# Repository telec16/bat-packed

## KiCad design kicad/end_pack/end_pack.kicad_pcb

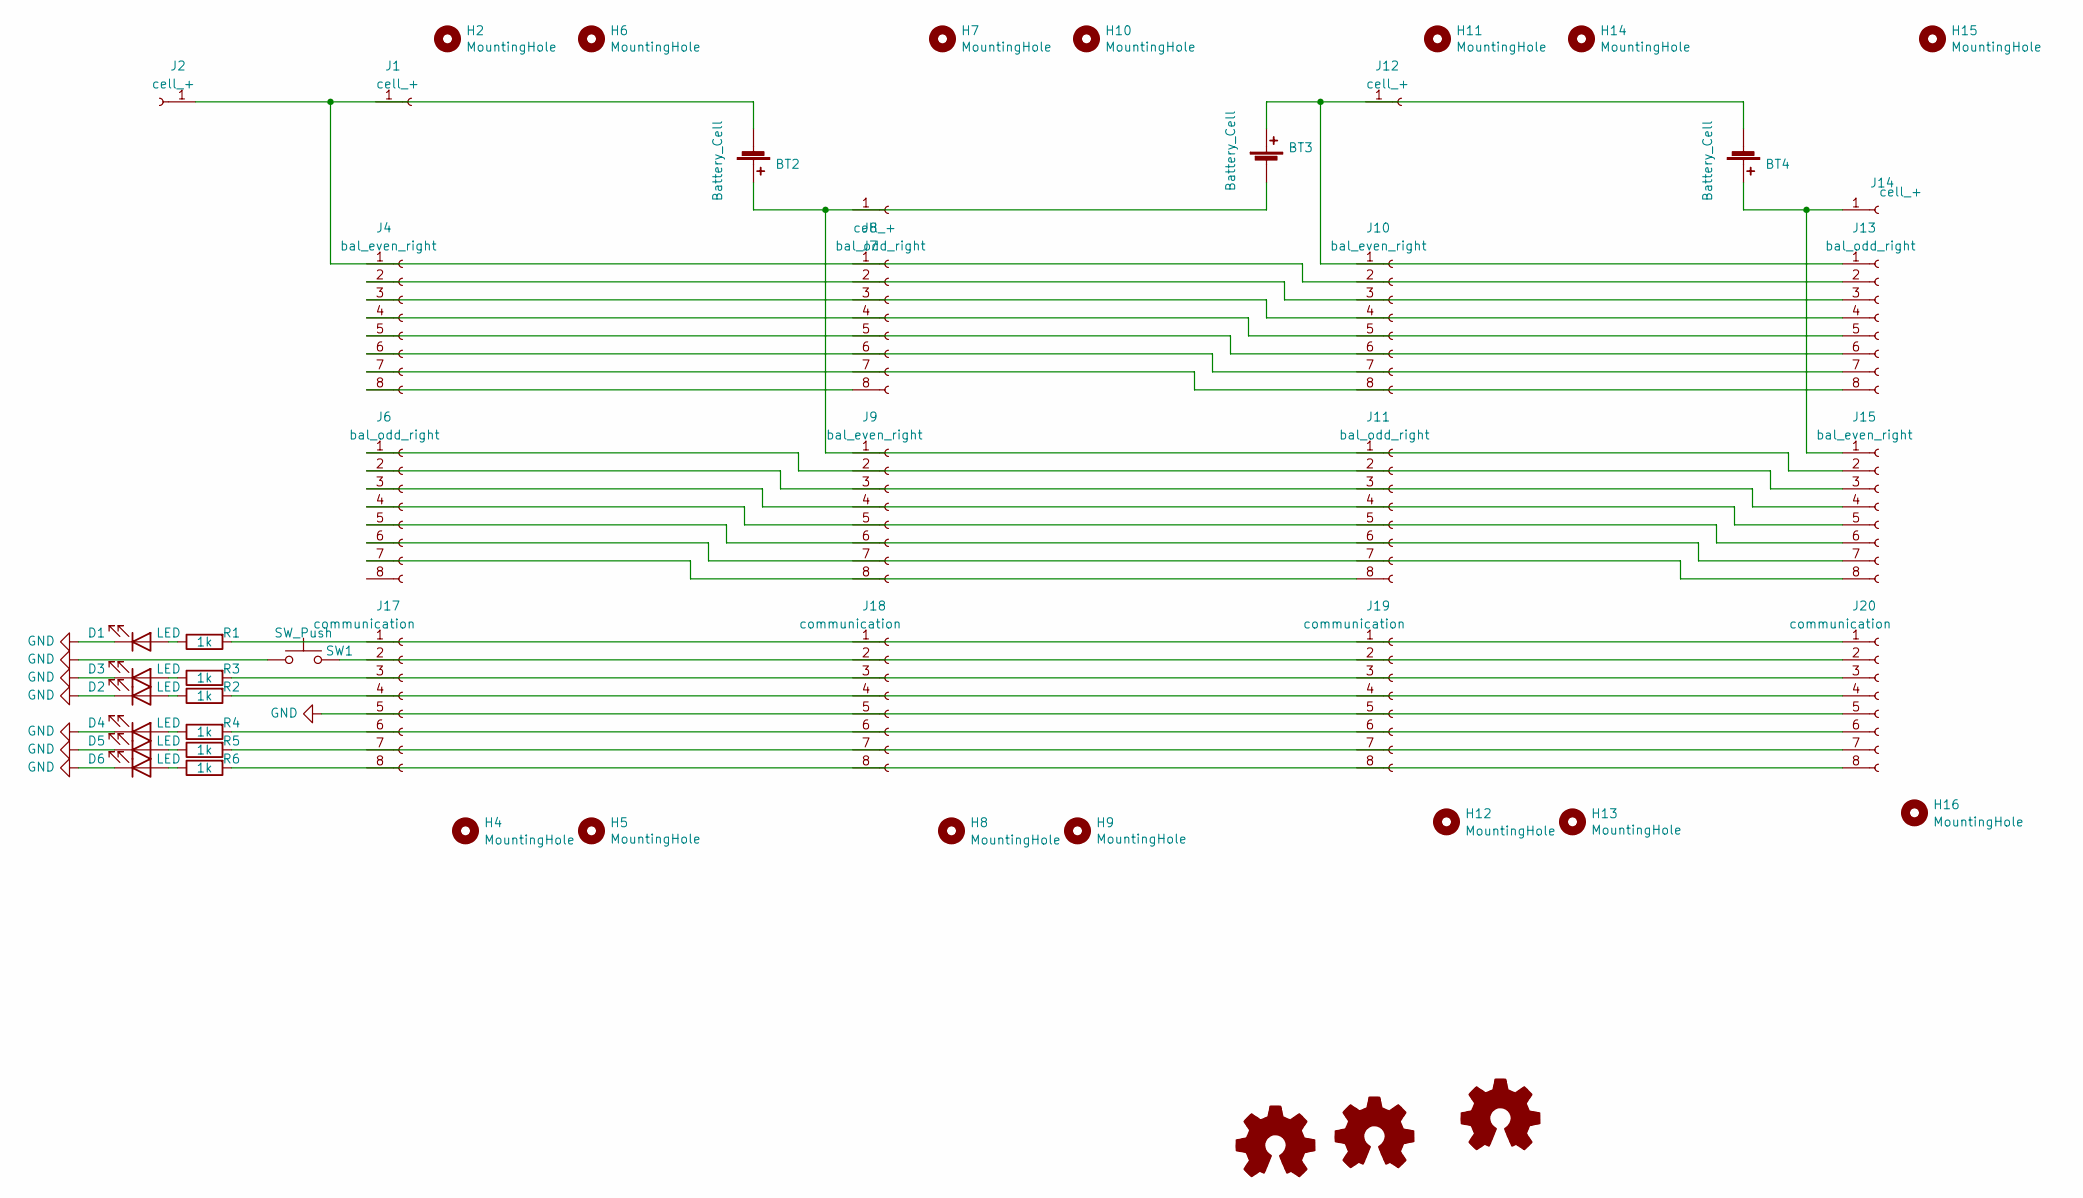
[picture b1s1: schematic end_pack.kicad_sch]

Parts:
BT2, BT3, BT4: Battery_Cell; Cell_18650
D1, D2, D3, D4, D5, D6: LED; LED_1206_3216Metric
H2, H4, H5, H6, H7, H8, H9, H10, H11, H12, H13, H14, H15, H16: MountingHole; MountingHole_2mm
J1, J7, J12: cell_+; Castellated_1x01_P5.08mm_Triple
J2: cell_+; Pin_D1.3mm_L11.0mm_LooseFit
J4, J9, J10, J15: bal_even_right; Castellated_1x08_P2.54mm
J6, J8, J11, J14: bal_odd_right; Castellated_1x08_P2.54mm
J13: cell_+; Castellated_1x01_P5.08mm_Double
J17, J18, J19, J20: communication; DualSide_2x05_P1.27mm_Vertical_SMD
LOGO1, LOGO2, LOGO3: Logo_Open_Hardware_Small; batpacked-24
R1, R2, R3, R4, R5, R6: 1k; R_0805_2012Metric
SW1: SW_Push; SW_Push_SPST_NO_Alps_SKRK

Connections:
GND: D1.1 (K), D2.1 (K), D3.1 (K), D4.1 (K), D5.1 (K), D6.1 (K), J20.5, SW1.2
unnamed: BT2.1 (+), BT3.2 (-), J15.2
unnamed: BT2.2 (-), J2.1, J14.2
unnamed: BT3.1 (+), BT4.2 (-), J14.1
unnamed: BT4.1 (+), J13.1, J15.1
unnamed: D1.2 (A), R1.1
unnamed: D2.2 (A), R2.1
unnamed: D3.2 (A), R3.1
unnamed: D4.2 (A), R4.1
unnamed: D5.2 (A), R5.1
unnamed: D6.2 (A), R6.1
unnamed: J4.8, J8.8
unnamed: J6.7, J11.8
unnamed: J4.2, J14.3
unnamed: J4.3, J14.4
unnamed: J4.4, J14.5
unnamed: J4.5, J14.6
unnamed: J4.6, J14.7
unnamed: J4.7, J14.8
unnamed: J6.1, J15.3
unnamed: J6.2, J15.4
unnamed: J6.3, J15.5
unnamed: J6.4, J15.6
unnamed: J6.5, J15.7
unnamed: J6.6, J15.8
unnamed: J20.1, R1.2
unnamed: J20.2, SW1.1
unnamed: J20.3, R3.2
unnamed: J20.4, R2.2
unnamed: J20.6, R4.2
unnamed: J20.7, R5.2
unnamed: J20.8, R6.2

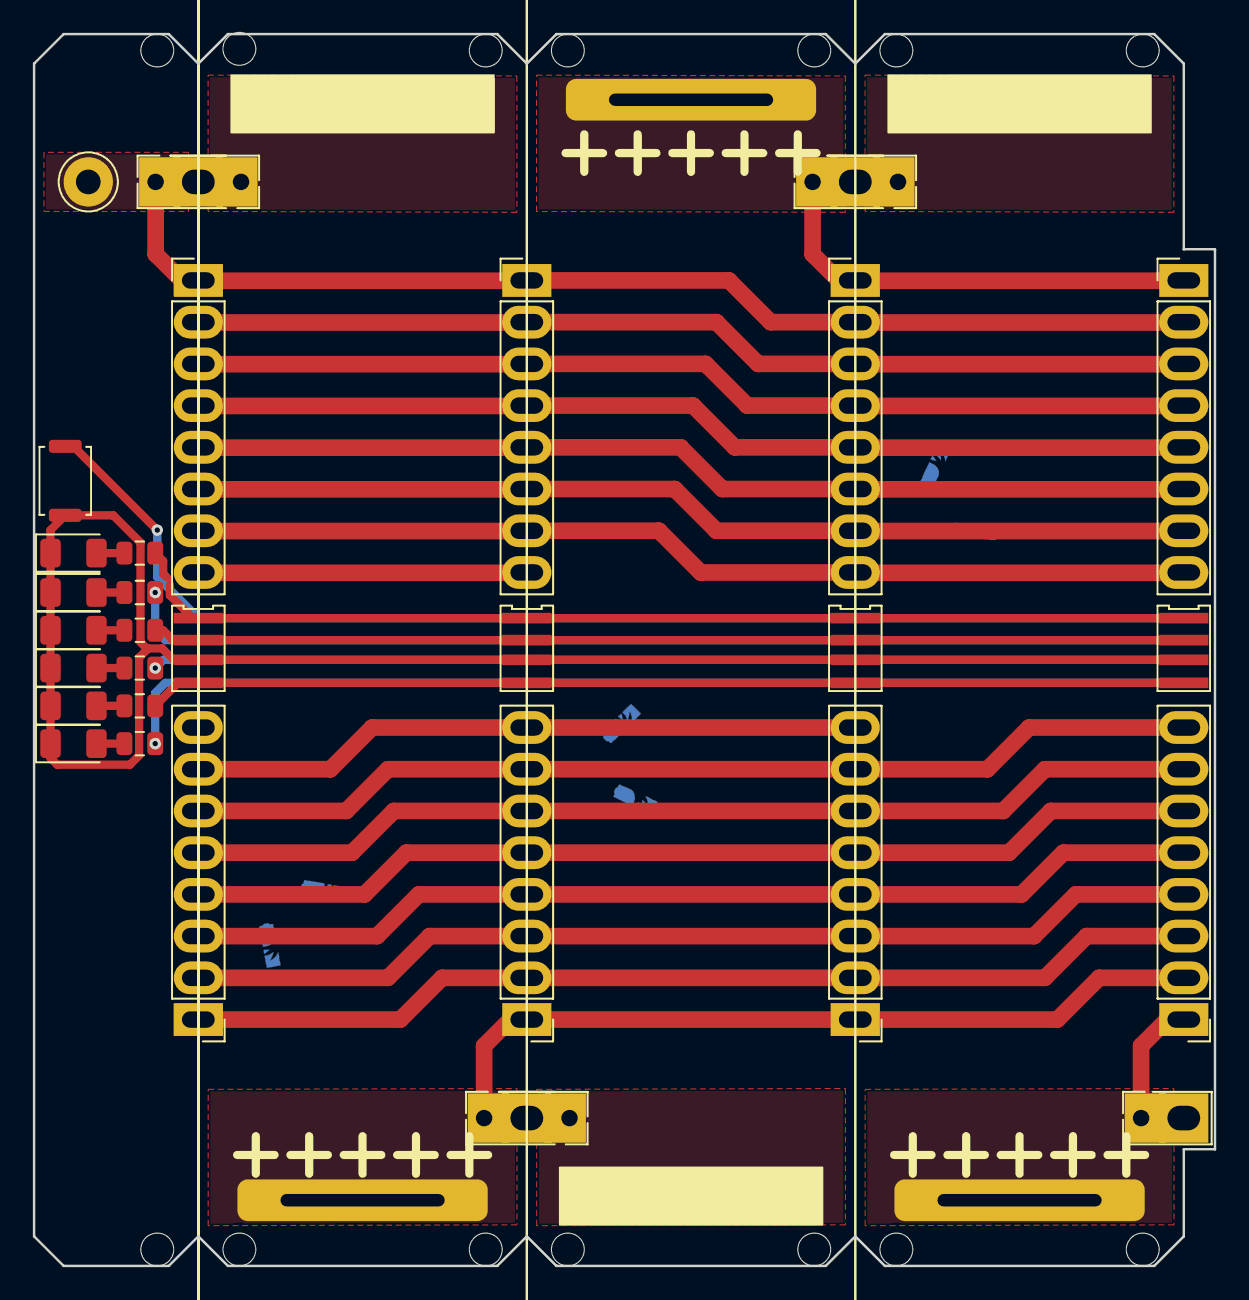
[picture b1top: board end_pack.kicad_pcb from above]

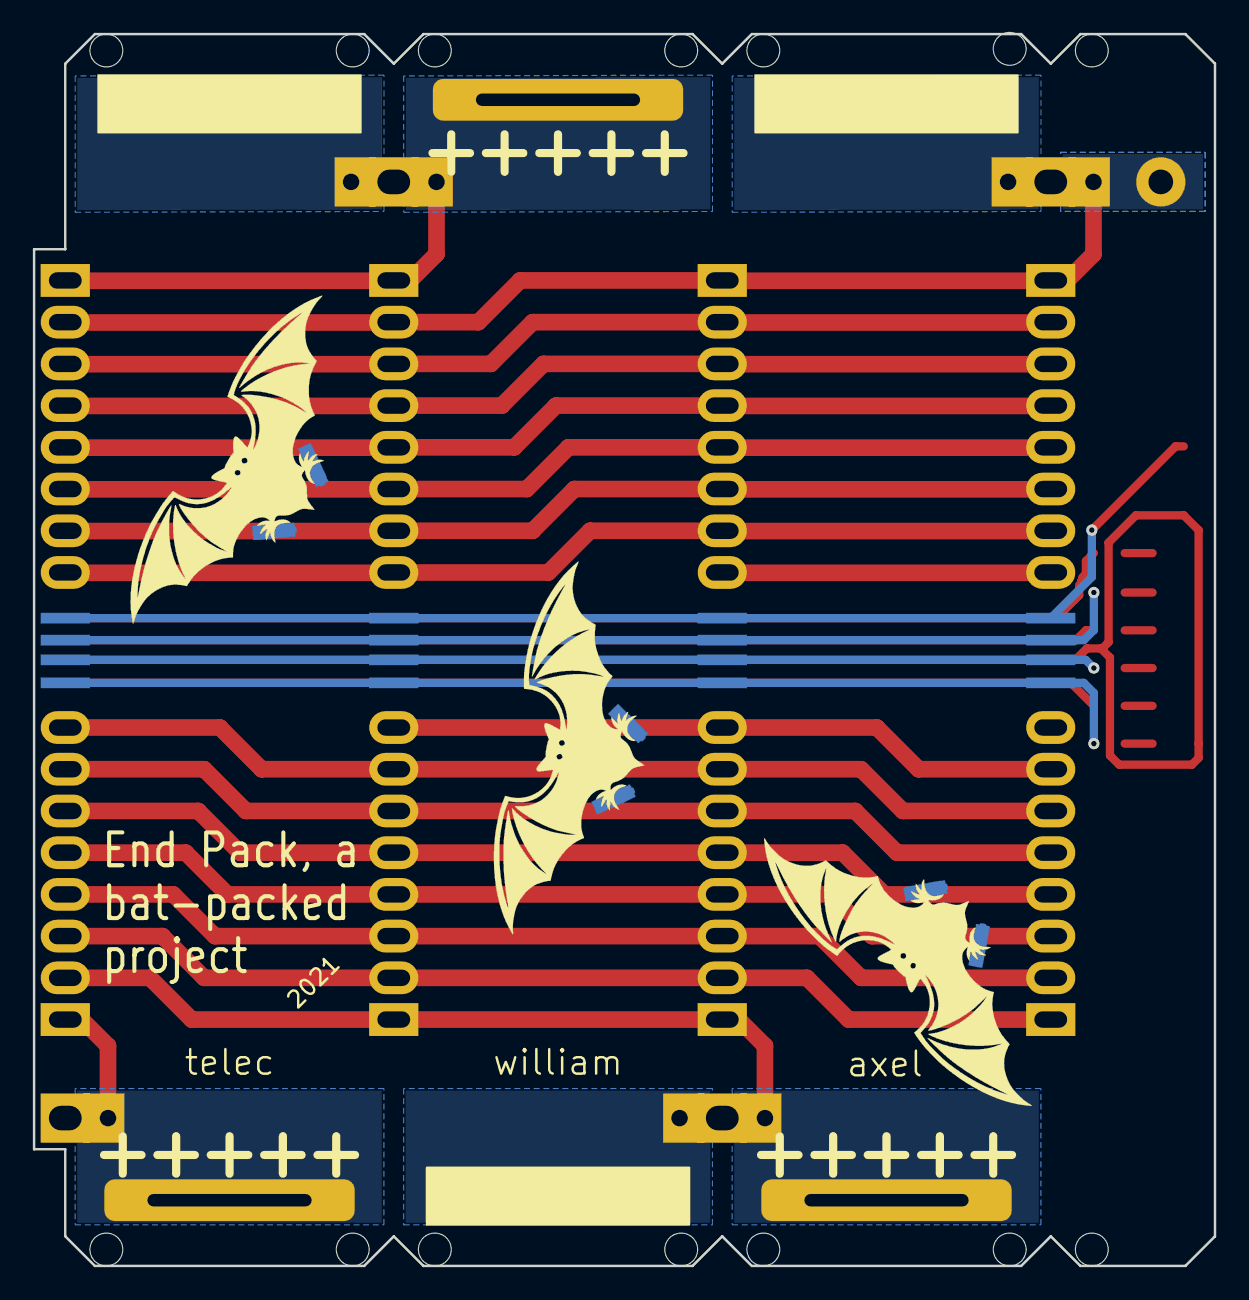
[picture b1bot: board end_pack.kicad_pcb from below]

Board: 2 copper layers, 71.9 x 75.0 mm, 50 parts (3 on the bottom side), 32 nets.

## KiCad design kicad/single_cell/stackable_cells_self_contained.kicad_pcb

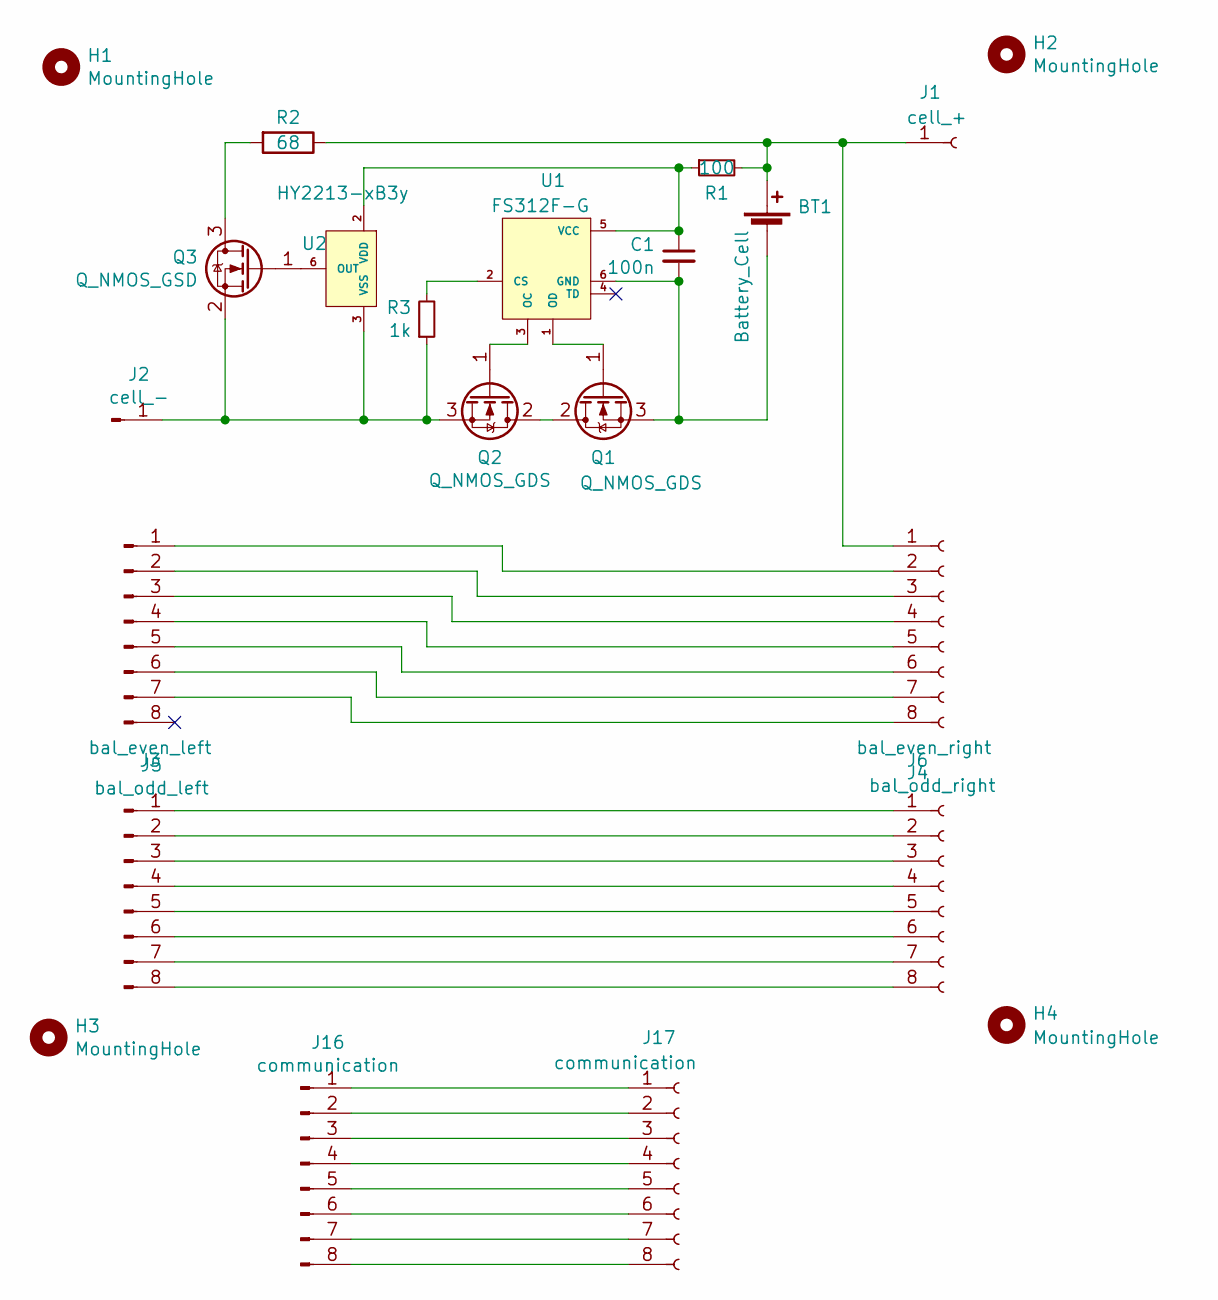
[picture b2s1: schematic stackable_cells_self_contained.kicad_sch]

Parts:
BT1: Battery_Cell; Cell_18650
C1: 100n; C_0603_1608Metric
H1, H2, H3, H4: MountingHole; MountingHole_2mm
J1: cell_+; Castellated_1x01_P5.08mm_Double
J2: cell_-; Castellated_1x01_P5.08mm_Double
J3: bal_even_left; Castellated_1x08_P2.54mm
J4: bal_even_right; Castellated_1x08_P2.54mm
J5: bal_odd_left; Castellated_1x08_P2.54mm
J6: bal_odd_right; Castellated_1x08_P2.54mm
J16, J17: communication; DualSide_2x05_P1.27mm_Vertical_SMD
Q1, Q2: Q_NMOS_GDS; TO-252-2
Q3: Q_NMOS_GSD; SOT-23
R1: 100; R_0603_1608Metric
R2: 68; R_1206_3216Metric
R3: 1k; R_0603_1608Metric
U1: FS312F-G; SOT-23-6
U2: HY2213-xB3y; SOT-23-6

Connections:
unnamed: BT1.1 (+), J1.1, J4.1, R1.2, R2.1
unnamed: BT1.2 (-), C1.2, Q1.3 (S), U1.6 (GND)
unnamed: J2.1, Q2.3 (S), Q3.2 (S), R3.1, U2.3 (VSS)
unnamed: J3.1, J4.2
unnamed: J3.2, J4.3
unnamed: J3.3, J4.4
unnamed: J3.4, J4.5
unnamed: J3.5, J4.6
unnamed: J3.6, J4.7
unnamed: J3.7, J4.8
unnamed: J5.1, J6.1
unnamed: J5.2, J6.2
unnamed: J5.3, J6.3
unnamed: J5.4, J6.4
unnamed: J5.5, J6.5
unnamed: J5.6, J6.6
unnamed: J5.7, J6.7
unnamed: J5.8, J6.8
unnamed: J16.1, J17.1
unnamed: J16.2, J17.2
unnamed: J16.3, J17.3
unnamed: J16.4, J17.4
unnamed: J16.5, J17.5
unnamed: J16.6, J17.6
unnamed: J16.7, J17.7
unnamed: J16.8, J17.8
unnamed: Q1.2 (D), Q2.2 (D)
unnamed: Q1.1 (G), U1.1 (OD)
unnamed: Q2.1 (G), U1.3 (OC)
unnamed: Q3.3 (D), R2.2
unnamed: Q3.1 (G), U2.6 (OUT)
unnamed: R3.2, U1.2 (CS)
unnamed: C1.1, R1.1, U1.5 (VCC), U2.2 (VDD)

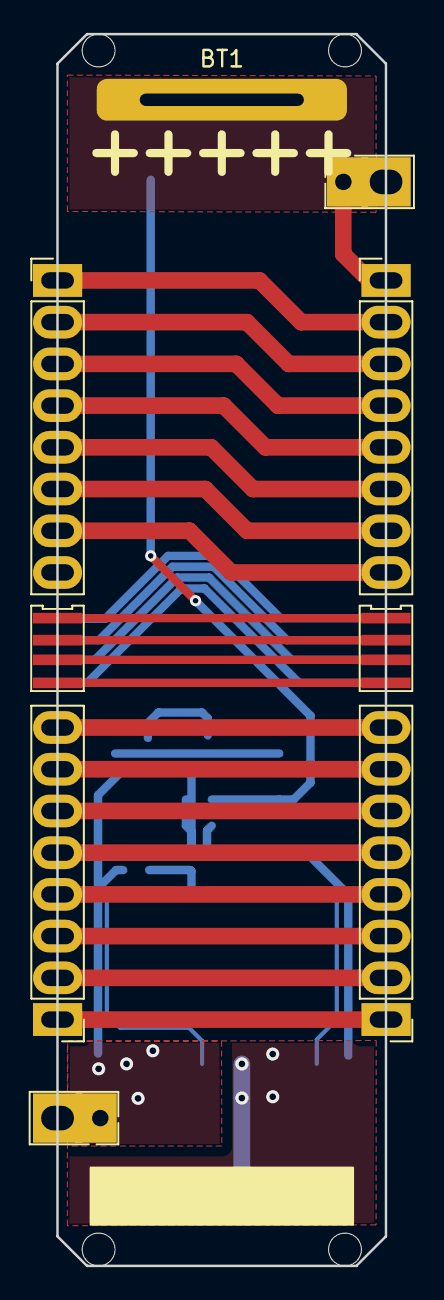
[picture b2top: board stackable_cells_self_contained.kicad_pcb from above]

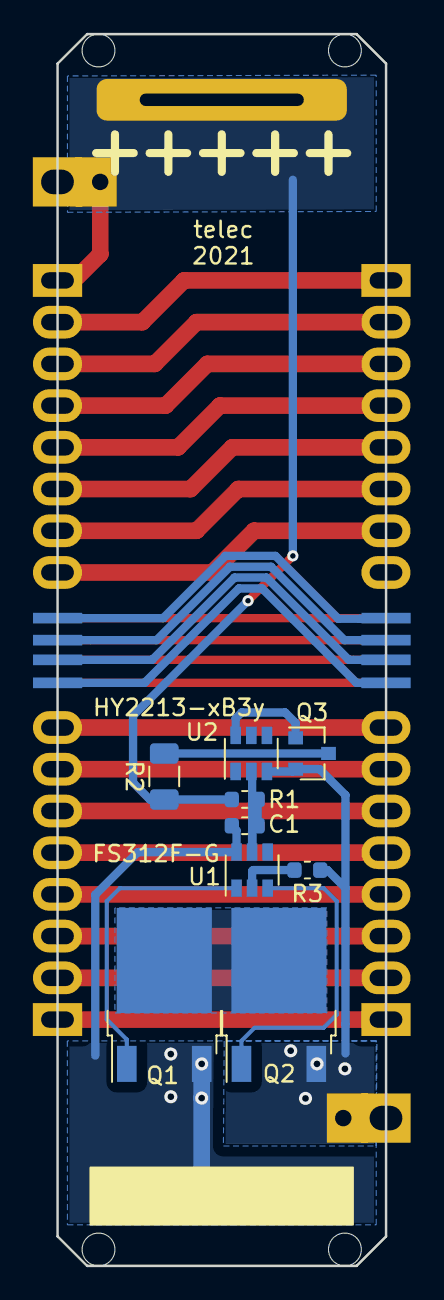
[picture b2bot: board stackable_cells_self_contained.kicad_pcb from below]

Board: 2 copper layers, 20.0 x 75.0 mm, 22 parts (9 on the bottom side), 33 nets.

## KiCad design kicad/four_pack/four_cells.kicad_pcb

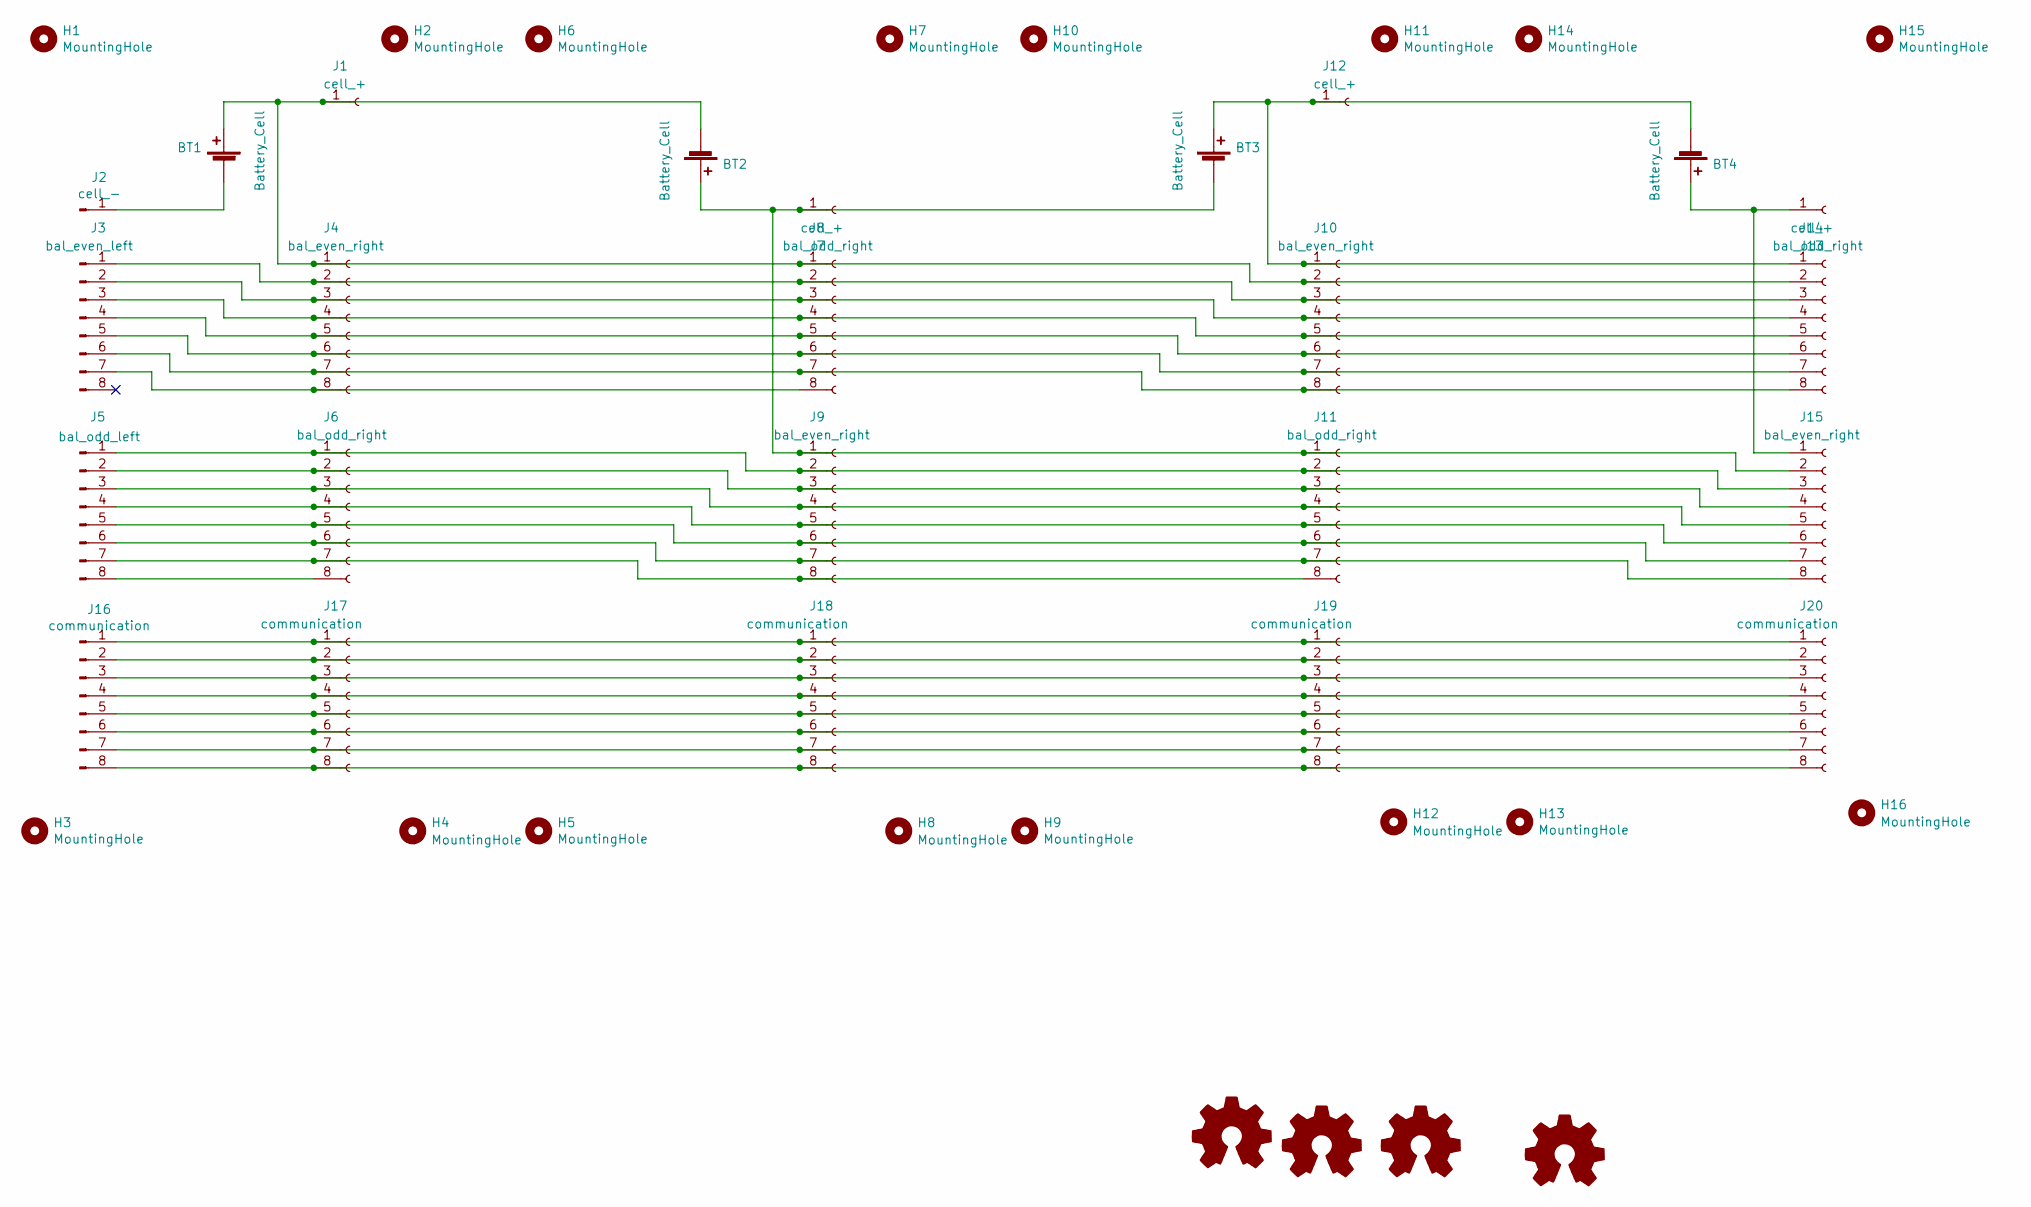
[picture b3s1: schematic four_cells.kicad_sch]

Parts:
BT1, BT2, BT3, BT4: Battery_Cell; Cell_18650
H1, H2, H3, H4, H5, H6, H7, H8, H9, H10, H11, H12, H13, H14, H15, H16: MountingHole; MountingHole_2mm
J1, J7, J12: cell_+; Castellated_1x01_P5.08mm_Triple
J2: cell_-; Castellated_1x01_P5.08mm_Double
J3: bal_even_left; Castellated_1x08_P2.54mm
J4, J9, J10, J15: bal_even_right; Castellated_1x08_P2.54mm
J5: bal_odd_left; Castellated_1x08_P2.54mm
J6, J8, J11, J14: bal_odd_right; Castellated_1x08_P2.54mm
J13: cell_+; Castellated_1x01_P5.08mm_Double
J16, J17, J18, J19, J20: communication; DualSide_2x05_P1.27mm_Vertical_SMD
LOGO1, LOGO2, LOGO3, LOGO4: Logo_Open_Hardware_Small; batpacked-24

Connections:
unnamed: BT1.1 (+), BT2.2 (-), J1.1, J4.1, J8.1, J10.2, J14.2
unnamed: BT1.2 (-), J2.1
unnamed: BT2.1 (+), BT3.2 (-), J7.1, J9.1, J11.1, J15.2
unnamed: BT3.1 (+), BT4.2 (-), J10.1, J12.1, J14.1
unnamed: BT4.1 (+), J13.1, J15.1
unnamed: J3.7, J4.8, J8.8
unnamed: J5.8, J6.8
unnamed: J3.1, J4.2, J8.2, J10.3, J14.3
unnamed: J3.2, J4.3, J8.3, J10.4, J14.4
unnamed: J3.3, J4.4, J8.4, J10.5, J14.5
unnamed: J3.4, J4.5, J8.5, J10.6, J14.6
unnamed: J3.5, J4.6, J8.6, J10.7, J14.7
unnamed: J3.6, J4.7, J8.7, J10.8, J14.8
unnamed: J5.1, J6.1, J9.2, J11.2, J15.3
unnamed: J5.2, J6.2, J9.3, J11.3, J15.4
unnamed: J5.3, J6.3, J9.4, J11.4, J15.5
unnamed: J5.4, J6.4, J9.5, J11.5, J15.6
unnamed: J5.5, J6.5, J9.6, J11.6, J15.7
unnamed: J5.6, J6.6, J9.7, J11.7, J15.8
unnamed: J5.7, J6.7, J9.8, J11.8
unnamed: J16.1, J17.1, J18.1, J19.1, J20.1
unnamed: J16.2, J17.2, J18.2, J19.2, J20.2
unnamed: J16.3, J17.3, J18.3, J19.3, J20.3
unnamed: J16.4, J17.4, J18.4, J19.4, J20.4
unnamed: J16.5, J17.5, J18.5, J19.5, J20.5
unnamed: J16.6, J17.6, J18.6, J19.6, J20.6
unnamed: J16.7, J17.7, J18.7, J19.7, J20.7
unnamed: J16.8, J17.8, J18.8, J19.8, J20.8

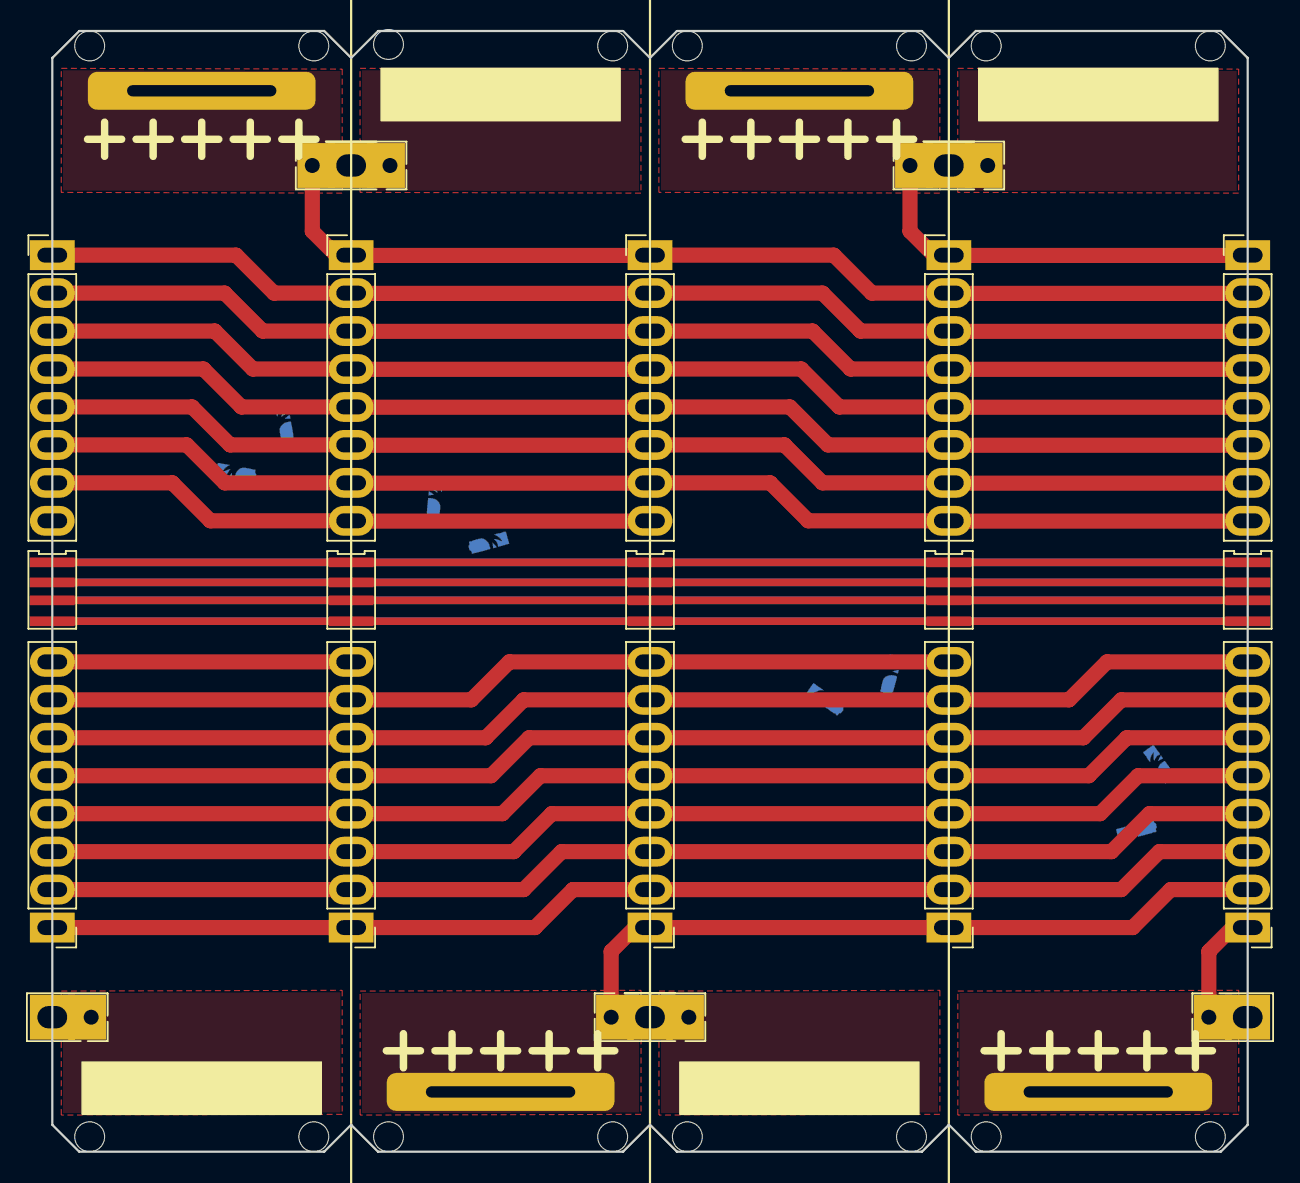
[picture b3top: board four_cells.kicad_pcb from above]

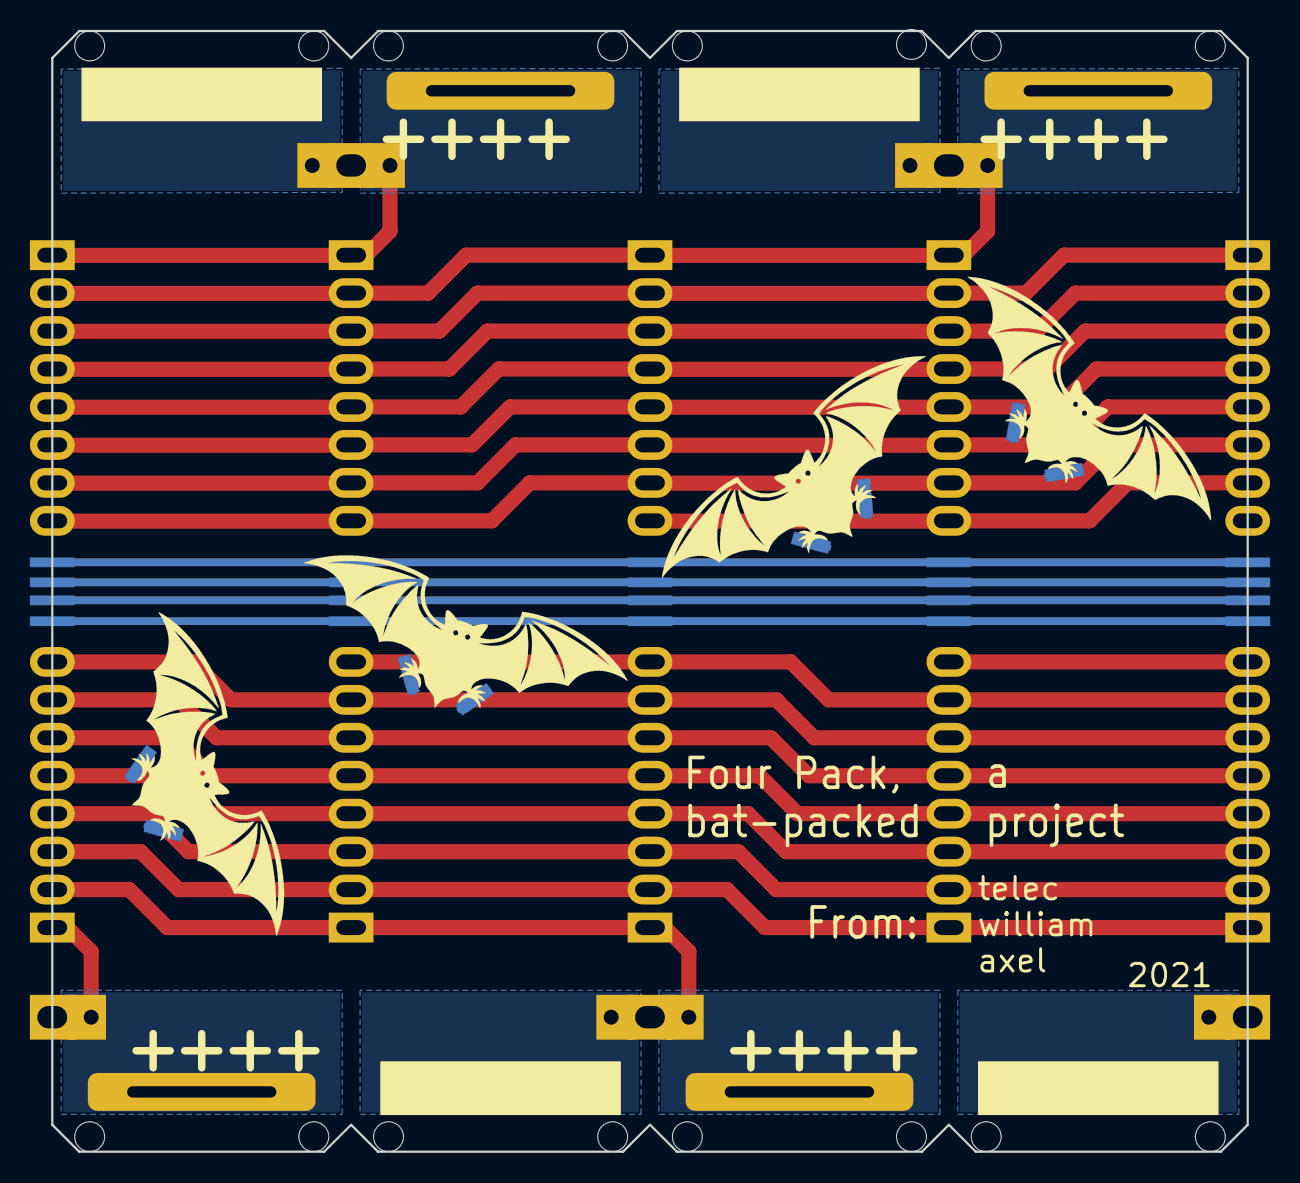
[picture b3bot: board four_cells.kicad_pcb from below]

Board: 2 copper layers, 80.0 x 75.0 mm, 44 parts (4 on the bottom side), 28 nets.

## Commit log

2021-04-27 microcontroller section + datasheet
2021-04-27 final choice ?
2021-04-27 stackable cell PCB
2021-04-27 self contained cell pcb
2021-04-28 Some assumptions on CAN
2021-04-28 Bad table...
2021-04-28 More doc!
2021-04-29 More info
2021-04-29 battery management draft
2021-04-29 Changed filetree
2021-04-29 more docs
2021-04-29 Finished four cells PCB
2021-04-30 Openscad model
2021-04-30 Pack model nearly done
2021-04-30 Pack model finished
2021-04-30 Small change
2021-04-30 added PCB model
2021-04-30 PCB 3D model
2021-04-30 Now with colors!
2021-04-30 Ending PCB finished
2021-04-30 Added end PCB
2021-04-30 added cell model
2021-05-04 Selected batteriy chippies
2021-05-05 Added docs
2021-05-09 Starting BMS PCB
2021-05-10 More on the charger
2021-07-26 gerber + logo
2021-07-26 finished stackable design
2021-07-27 silkscreen correction
2021-07-28 fix silkscreen + hole location
2023-06-22 Updated to kicad 7.x
